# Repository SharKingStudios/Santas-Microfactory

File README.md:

# Santas Microfactory
A factory game built entirely out of diode transistor logic.

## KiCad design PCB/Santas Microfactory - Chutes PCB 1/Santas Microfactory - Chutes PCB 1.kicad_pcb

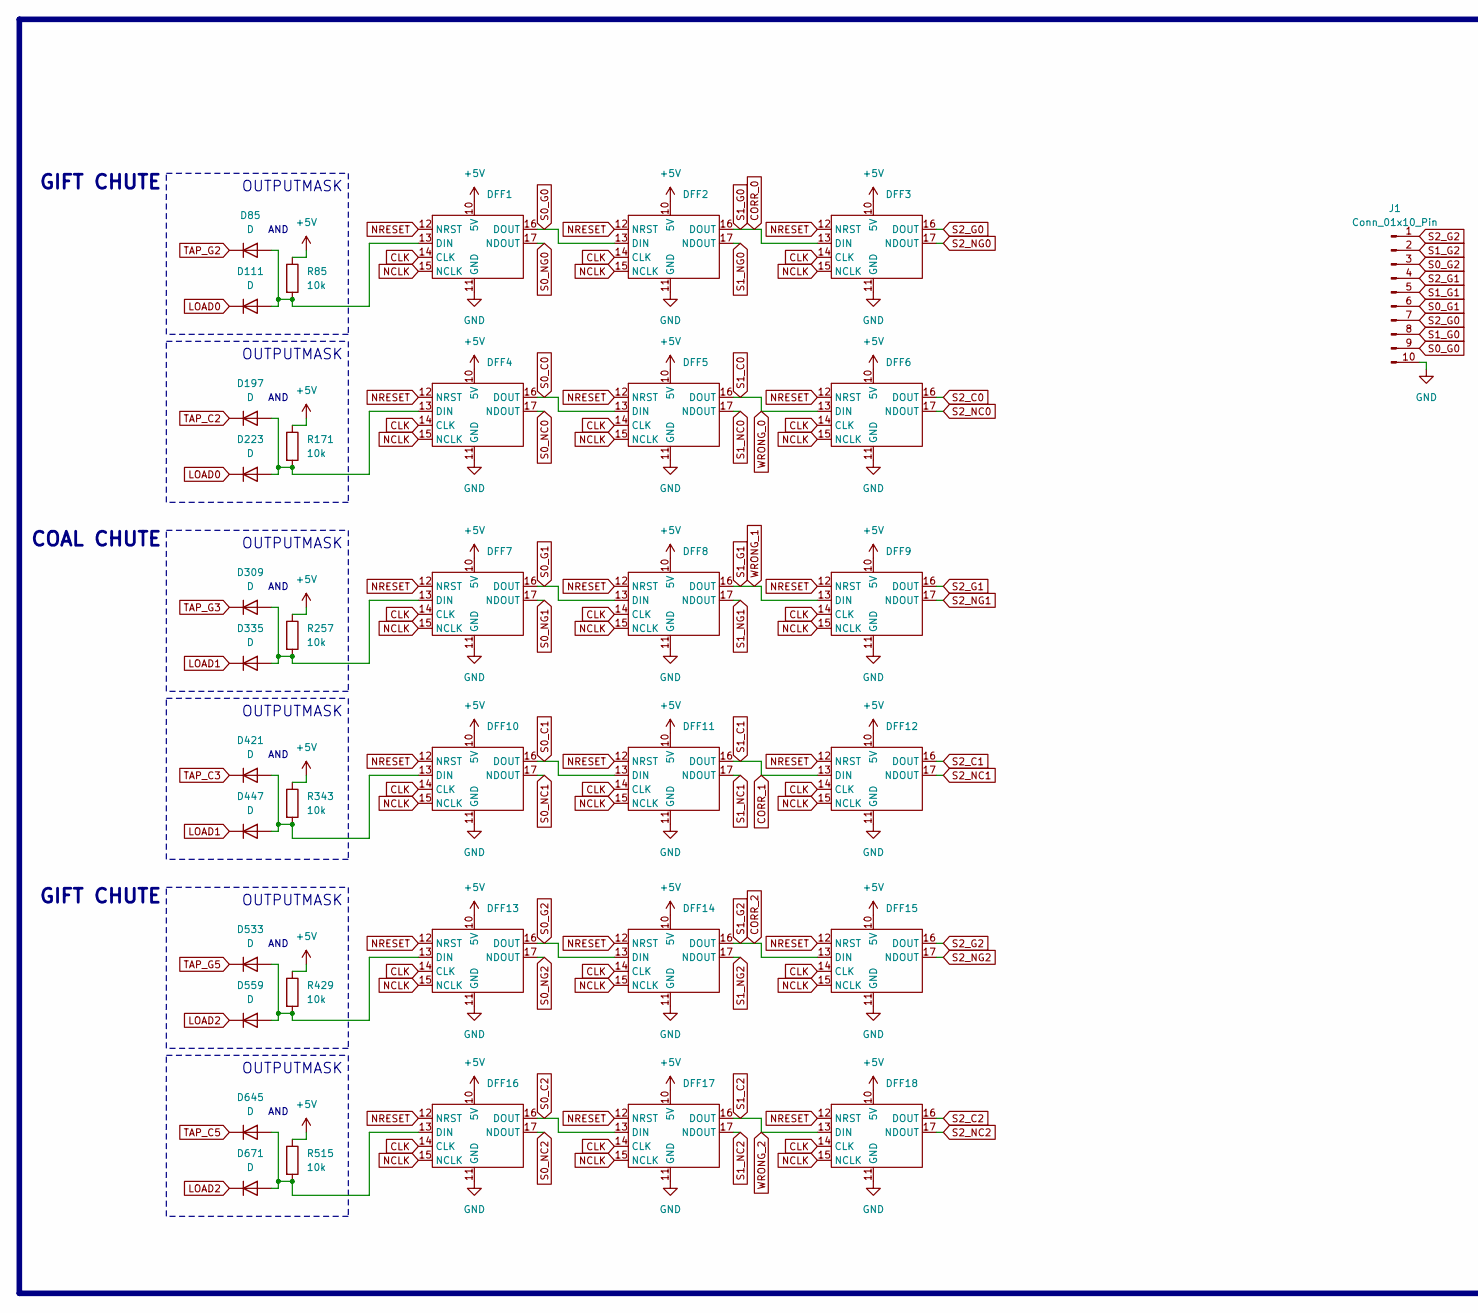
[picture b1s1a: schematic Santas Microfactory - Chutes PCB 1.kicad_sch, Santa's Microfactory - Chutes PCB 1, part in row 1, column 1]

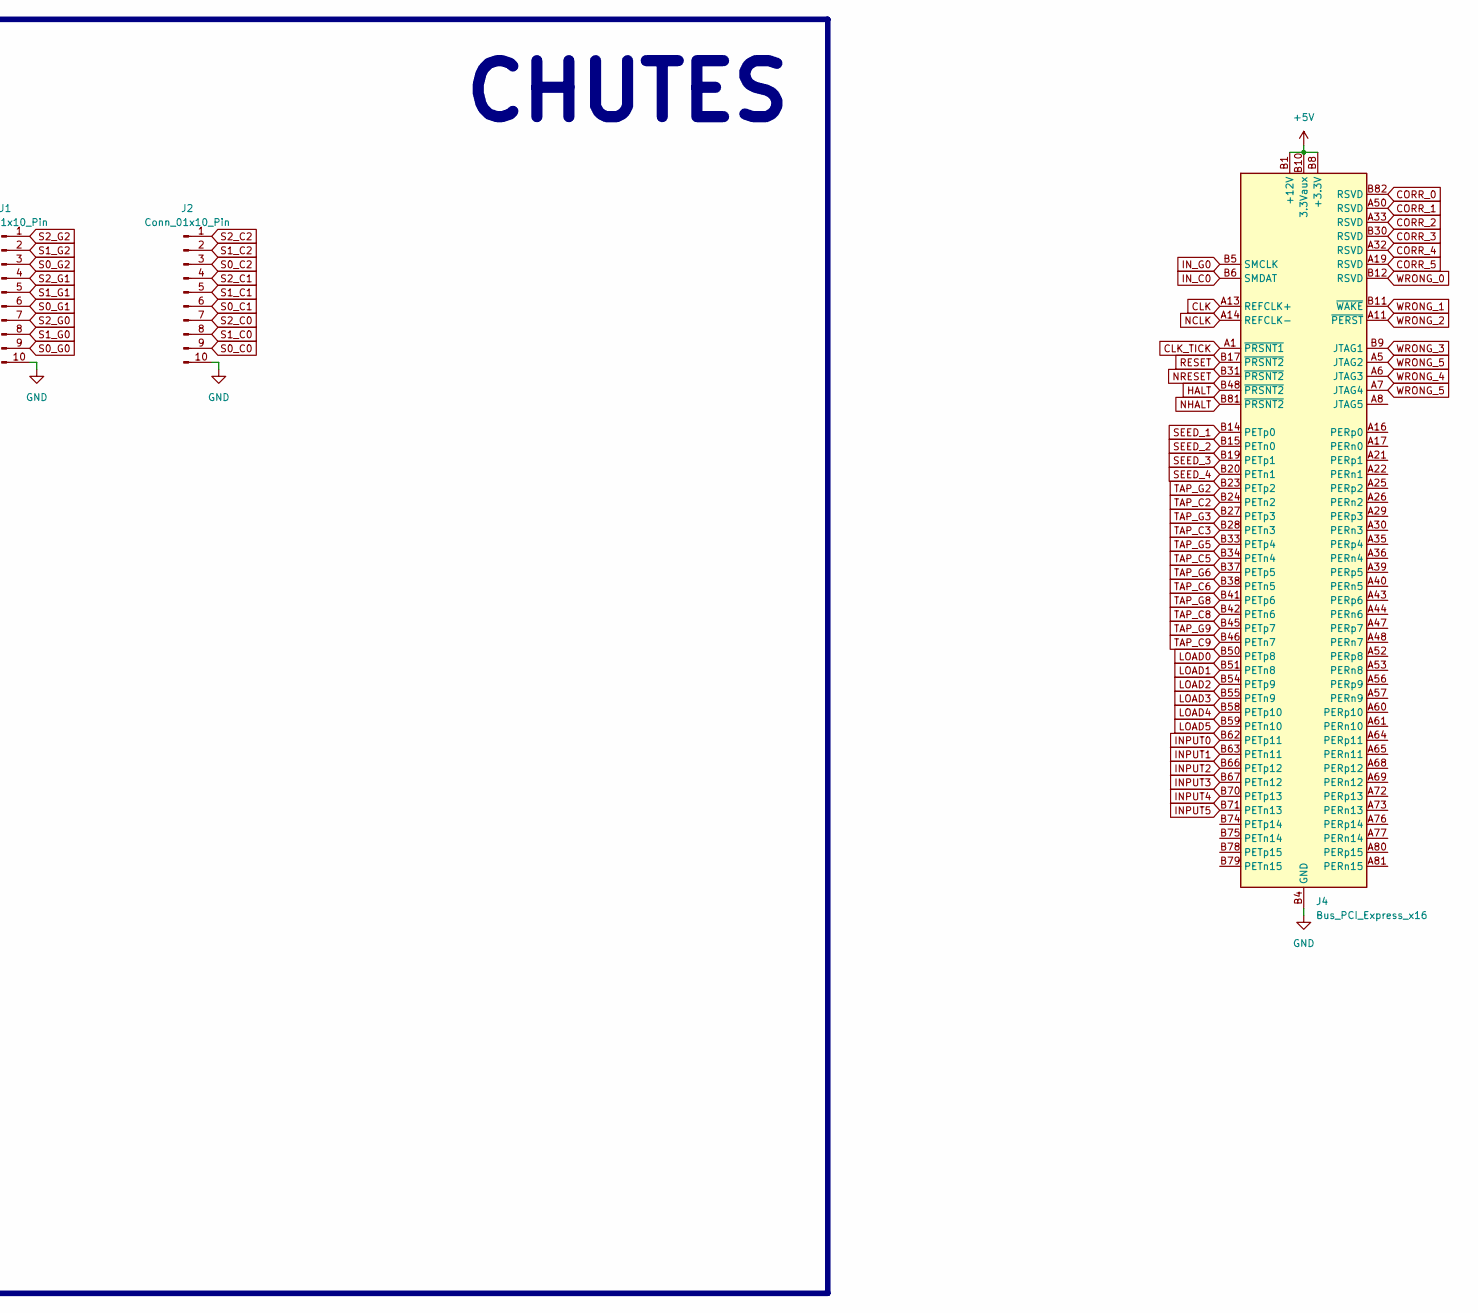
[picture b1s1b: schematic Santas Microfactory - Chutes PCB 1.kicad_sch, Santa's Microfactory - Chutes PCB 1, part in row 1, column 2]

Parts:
D85, D111, D197, D223, D309, D335, D421, D447, D533, D559, D645, D671: D; D_DO-35_SOD27_P2.54mm_Vertical_AnodeUp
DFF1, DFF2, DFF3, DFF4, DFF5, DFF6, DFF7, DFF8, DFF9, DFF10, DFF11, DFF12, DFF13, DFF14, DFF15, DFF16, DFF17, DFF18: DFF-shenanigans
J1, J2: Conn_01x10_Pin; PinHeader_1x10_P2.54mm_Horizontal
J4: Bus_PCI_Express_x16; BUS_PCIexpress_x16
R85, R171, R257, R343, R429, R515: 10k; R_Axial_DIN0207_L6.3mm_D2.5mm_P2.54mm_Vertical

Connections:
+5V: DFF1.10 (5V), DFF2.10 (5V), DFF3.10 (5V), DFF4.10 (5V), DFF5.10 (5V), DFF6.10 (5V), DFF7.10 (5V), DFF8.10 (5V), DFF9.10 (5V), DFF10.10 (5V), DFF11.10 (5V), DFF12.10 (5V), DFF13.10 (5V), DFF14.10 (5V), DFF15.10 (5V), DFF16.10 (5V), DFF17.10 (5V), DFF18.10 (5V), J4.A2 (+12V), J4.A3 (+12V), J4.A9 (+3.3V), J4.A10 (+3.3V), J4.B1 (+12V), J4.B2 (+12V), J4.B3 (+12V), J4.B8 (+3.3V), J4.B10 (3.3Vaux), R85.1, R171.1, R257.1, R343.1, R429.1, R515.1
CLK: DFF1.14 (CLK), DFF2.14 (CLK), DFF3.14 (CLK), DFF4.14 (CLK), DFF5.14 (CLK), DFF6.14 (CLK), DFF7.14 (CLK), DFF8.14 (CLK), DFF9.14 (CLK), DFF10.14 (CLK), DFF11.14 (CLK), DFF12.14 (CLK), DFF13.14 (CLK), DFF14.14 (CLK), DFF15.14 (CLK), DFF16.14 (CLK), DFF17.14 (CLK), DFF18.14 (CLK), J4.A13 (REFCLK+)
CLK_TICK: J4.A1 (~PRSNT1)
CORR_0: DFF2.16 (DOUT), DFF3.13 (DIN), J1.8, J4.B82 (RSVD)
CORR_1: DFF11.16 (DOUT), DFF12.13 (DIN), J2.5, J4.A50 (RSVD)
CORR_2: DFF14.16 (DOUT), DFF15.13 (DIN), J1.2, J4.A33 (RSVD)
CORR_3: J4.B30 (RSVD)
CORR_4: J4.A32 (RSVD)
CORR_5: J4.A19 (RSVD)
GND: DFF1.11 (GND), DFF2.11 (GND), DFF3.11 (GND), DFF4.11 (GND), DFF5.11 (GND), DFF6.11 (GND), DFF7.11 (GND), DFF8.11 (GND), DFF9.11 (GND), DFF10.11 (GND), DFF11.11 (GND), DFF12.11 (GND), DFF13.11 (GND), DFF14.11 (GND), DFF15.11 (GND), DFF16.11 (GND), DFF17.11 (GND), DFF18.11 (GND), J1.10, J2.10, J4.A4 (GND), J4.A12 (GND), J4.A15 (GND), J4.A18 (GND), J4.A20 (GND), J4.A23 (GND), J4.A24 (GND), J4.A27 (GND), J4.A28 (GND), J4.A31 (GND), J4.A34 (GND), J4.A37 (GND), J4.A38 (GND), J4.A41 (GND), J4.A42 (GND), J4.A45 (GND), J4.A46 (GND), J4.A49 (GND), J4.A51 (GND), J4.A54 (GND), J4.A55 (GND), J4.A58 (GND), J4.A59 (GND), J4.A62 (GND), J4.A63 (GND), J4.A66 (GND), J4.A67 (GND), J4.A70 (GND), J4.A71 (GND), J4.A74 (GND), J4.A75 (GND), J4.A78 (GND), J4.A79 (GND), J4.A82 (GND), J4.B4 (GND), J4.B7 (GND), J4.B13 (GND), J4.B16 (GND), J4.B18 (GND), J4.B21 (GND), J4.B22 (GND), J4.B25 (GND), J4.B26 (GND), J4.B29 (GND), J4.B32 (GND), J4.B35 (GND), J4.B36 (GND), J4.B39 (GND), J4.B40 (GND), J4.B43 (GND), J4.B44 (GND), J4.B47 (GND), J4.B49 (GND), J4.B52 (GND), J4.B53 (GND), J4.B56 (GND), J4.B57 (GND), J4.B60 (GND), J4.B61 (GND), J4.B64 (GND), J4.B65 (GND), J4.B68 (GND), J4.B69 (GND), J4.B72 (GND), J4.B73 (GND), J4.B76 (GND), J4.B77 (GND), J4.B80 (GND)
HALT: J4.B48 (~PRSNT2)
INPUT0: J4.B62 (PETp11)
INPUT1: J4.B63 (PETn11)
INPUT2: J4.B66 (PETp12)
INPUT3: J4.B67 (PETn12)
INPUT4: J4.B70 (PETp13)
INPUT5: J4.B71 (PETn13)
IN_C0: J4.B6 (SMDAT)
IN_G0: J4.B5 (SMCLK)
LOAD0: D111.1 (K), D223.1 (K), J4.B50 (PETp8)
LOAD1: D335.1 (K), D447.1 (K), J4.B51 (PETn8)
LOAD2: D559.1 (K), D671.1 (K), J4.B54 (PETp9)
LOAD3: J4.B55 (PETn9)
LOAD4: J4.B58 (PETp10)
LOAD5: J4.B59 (PETn10)
NCLK: DFF1.15 (NCLK), DFF2.15 (NCLK), DFF3.15 (NCLK), DFF4.15 (NCLK), DFF5.15 (NCLK), DFF6.15 (NCLK), DFF7.15 (NCLK), DFF8.15 (NCLK), DFF9.15 (NCLK), DFF10.15 (NCLK), DFF11.15 (NCLK), DFF12.15 (NCLK), DFF13.15 (NCLK), DFF14.15 (NCLK), DFF15.15 (NCLK), DFF16.15 (NCLK), DFF17.15 (NCLK), DFF18.15 (NCLK), J4.A14 (REFCLK-)
NHALT: J4.B81 (~PRSNT2)
NRESET: DFF1.12 (NRST), DFF2.12 (NRST), DFF3.12 (NRST), DFF4.12 (NRST), DFF5.12 (NRST), DFF6.12 (NRST), DFF7.12 (NRST), DFF8.12 (NRST), DFF9.12 (NRST), DFF10.12 (NRST), DFF11.12 (NRST), DFF12.12 (NRST), DFF13.12 (NRST), DFF14.12 (NRST), DFF15.12 (NRST), DFF16.12 (NRST), DFF17.12 (NRST), DFF18.12 (NRST), J4.B31 (~PRSNT2)
unnamed: D85.2 (A), D111.2 (A), DFF1.13 (DIN), R85.2
unnamed: D197.2 (A), D223.2 (A), DFF4.13 (DIN), R171.2
unnamed: D309.2 (A), D335.2 (A), DFF7.13 (DIN), R257.2
unnamed: D421.2 (A), D447.2 (A), DFF10.13 (DIN), R343.2
unnamed: D533.2 (A), D559.2 (A), DFF13.13 (DIN), R429.2
unnamed: D645.2 (A), D671.2 (A), DFF16.13 (DIN), R515.2
RESET: J4.B17 (~PRSNT2)
S0_C0: DFF4.16 (DOUT), DFF5.13 (DIN), J2.9
S0_C1: DFF10.16 (DOUT), DFF11.13 (DIN), J2.6
S0_C2: DFF16.16 (DOUT), DFF17.13 (DIN), J2.3
S0_G0: DFF1.16 (DOUT), DFF2.13 (DIN), J1.9
S0_G1: DFF7.16 (DOUT), DFF8.13 (DIN), J1.6
S0_G2: DFF13.16 (DOUT), DFF14.13 (DIN), J1.3
S0_NC0: DFF4.17 (NDOUT)
S0_NC1: DFF10.17 (NDOUT)
S0_NC2: DFF16.17 (NDOUT)
S0_NG0: DFF1.17 (NDOUT)
S0_NG1: DFF7.17 (NDOUT)
S0_NG2: DFF13.17 (NDOUT)
S1_C0: DFF5.16 (DOUT), DFF6.13 (DIN), J2.8, J4.B12 (RSVD)
S1_C2: DFF17.16 (DOUT), DFF18.13 (DIN), J2.2, J4.A11 (~PERST)
S1_G1: DFF8.16 (DOUT), DFF9.13 (DIN), J1.5, J4.B11 (~WAKE)
S1_NC0: DFF5.17 (NDOUT)
S1_NC1: DFF11.17 (NDOUT)
S1_NC2: DFF17.17 (NDOUT)
S1_NG0: DFF2.17 (NDOUT)
S1_NG1: DFF8.17 (NDOUT)
S1_NG2: DFF14.17 (NDOUT)
S2_C0: DFF6.16 (DOUT), J2.7
S2_C1: DFF12.16 (DOUT), J2.4
S2_C2: DFF18.16 (DOUT), J2.1
S2_G0: DFF3.16 (DOUT), J1.7
S2_G1: DFF9.16 (DOUT), J1.4
S2_G2: DFF15.16 (DOUT), J1.1
S2_NC0: DFF6.17 (NDOUT)
S2_NC1: DFF12.17 (NDOUT)
S2_NC2: DFF18.17 (NDOUT)
S2_NG0: DFF3.17 (NDOUT)
S2_NG1: DFF9.17 (NDOUT)
S2_NG2: DFF15.17 (NDOUT)
SEED_1: J4.B14 (PETp0)
SEED_2: J4.B15 (PETn0)
SEED_3: J4.B19 (PETp1)
SEED_4: J4.B20 (PETn1)
TAP_C2: D197.1 (K), J4.B24 (PETn2)
TAP_C3: D421.1 (K), J4.B28 (PETn3)
TAP_C5: D645.1 (K), J4.B34 (PETn4)
TAP_C6: J4.B38 (PETn5)
TAP_C8: J4.B42 (PETn6)
TAP_C9: J4.B46 (PETn7)
TAP_G2: D85.1 (K), J4.B23 (PETp2)
TAP_G3: D309.1 (K), J4.B27 (PETp3)
TAP_G5: D533.1 (K), J4.B33 (PETp4)
TAP_G6: J4.B37 (PETp5)
TAP_G8: J4.B41 (PETp6)
TAP_G9: J4.B45 (PETp7)
WRONG_3: J4.B9 (JTAG1)
WRONG_4: J4.A6 (JTAG3)
WRONG_5: J4.A5 (JTAG2), J4.A7 (JTAG4)

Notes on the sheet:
AND
OUTPUTMASK
GIFT CHUTE
COAL CHUTE
CHUTES

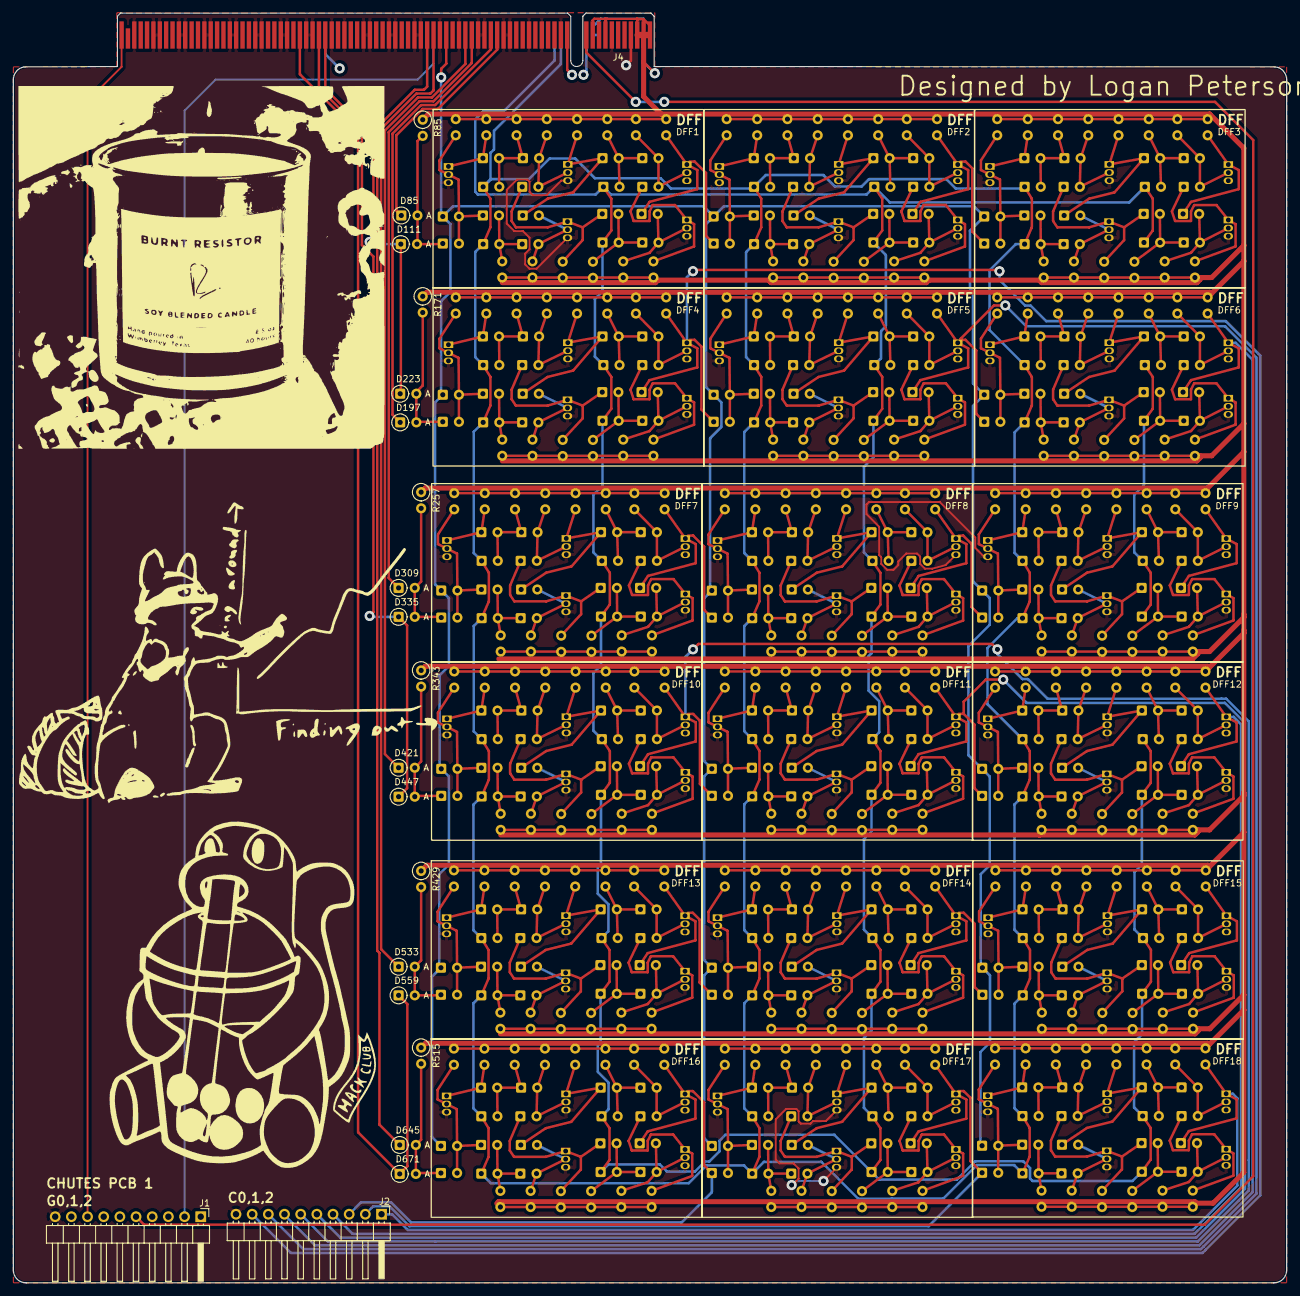
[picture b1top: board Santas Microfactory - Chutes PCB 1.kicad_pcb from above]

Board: 4 copper layers, 200.0 x 199.4 mm, 39 parts (0 on the bottom side), 39 nets.

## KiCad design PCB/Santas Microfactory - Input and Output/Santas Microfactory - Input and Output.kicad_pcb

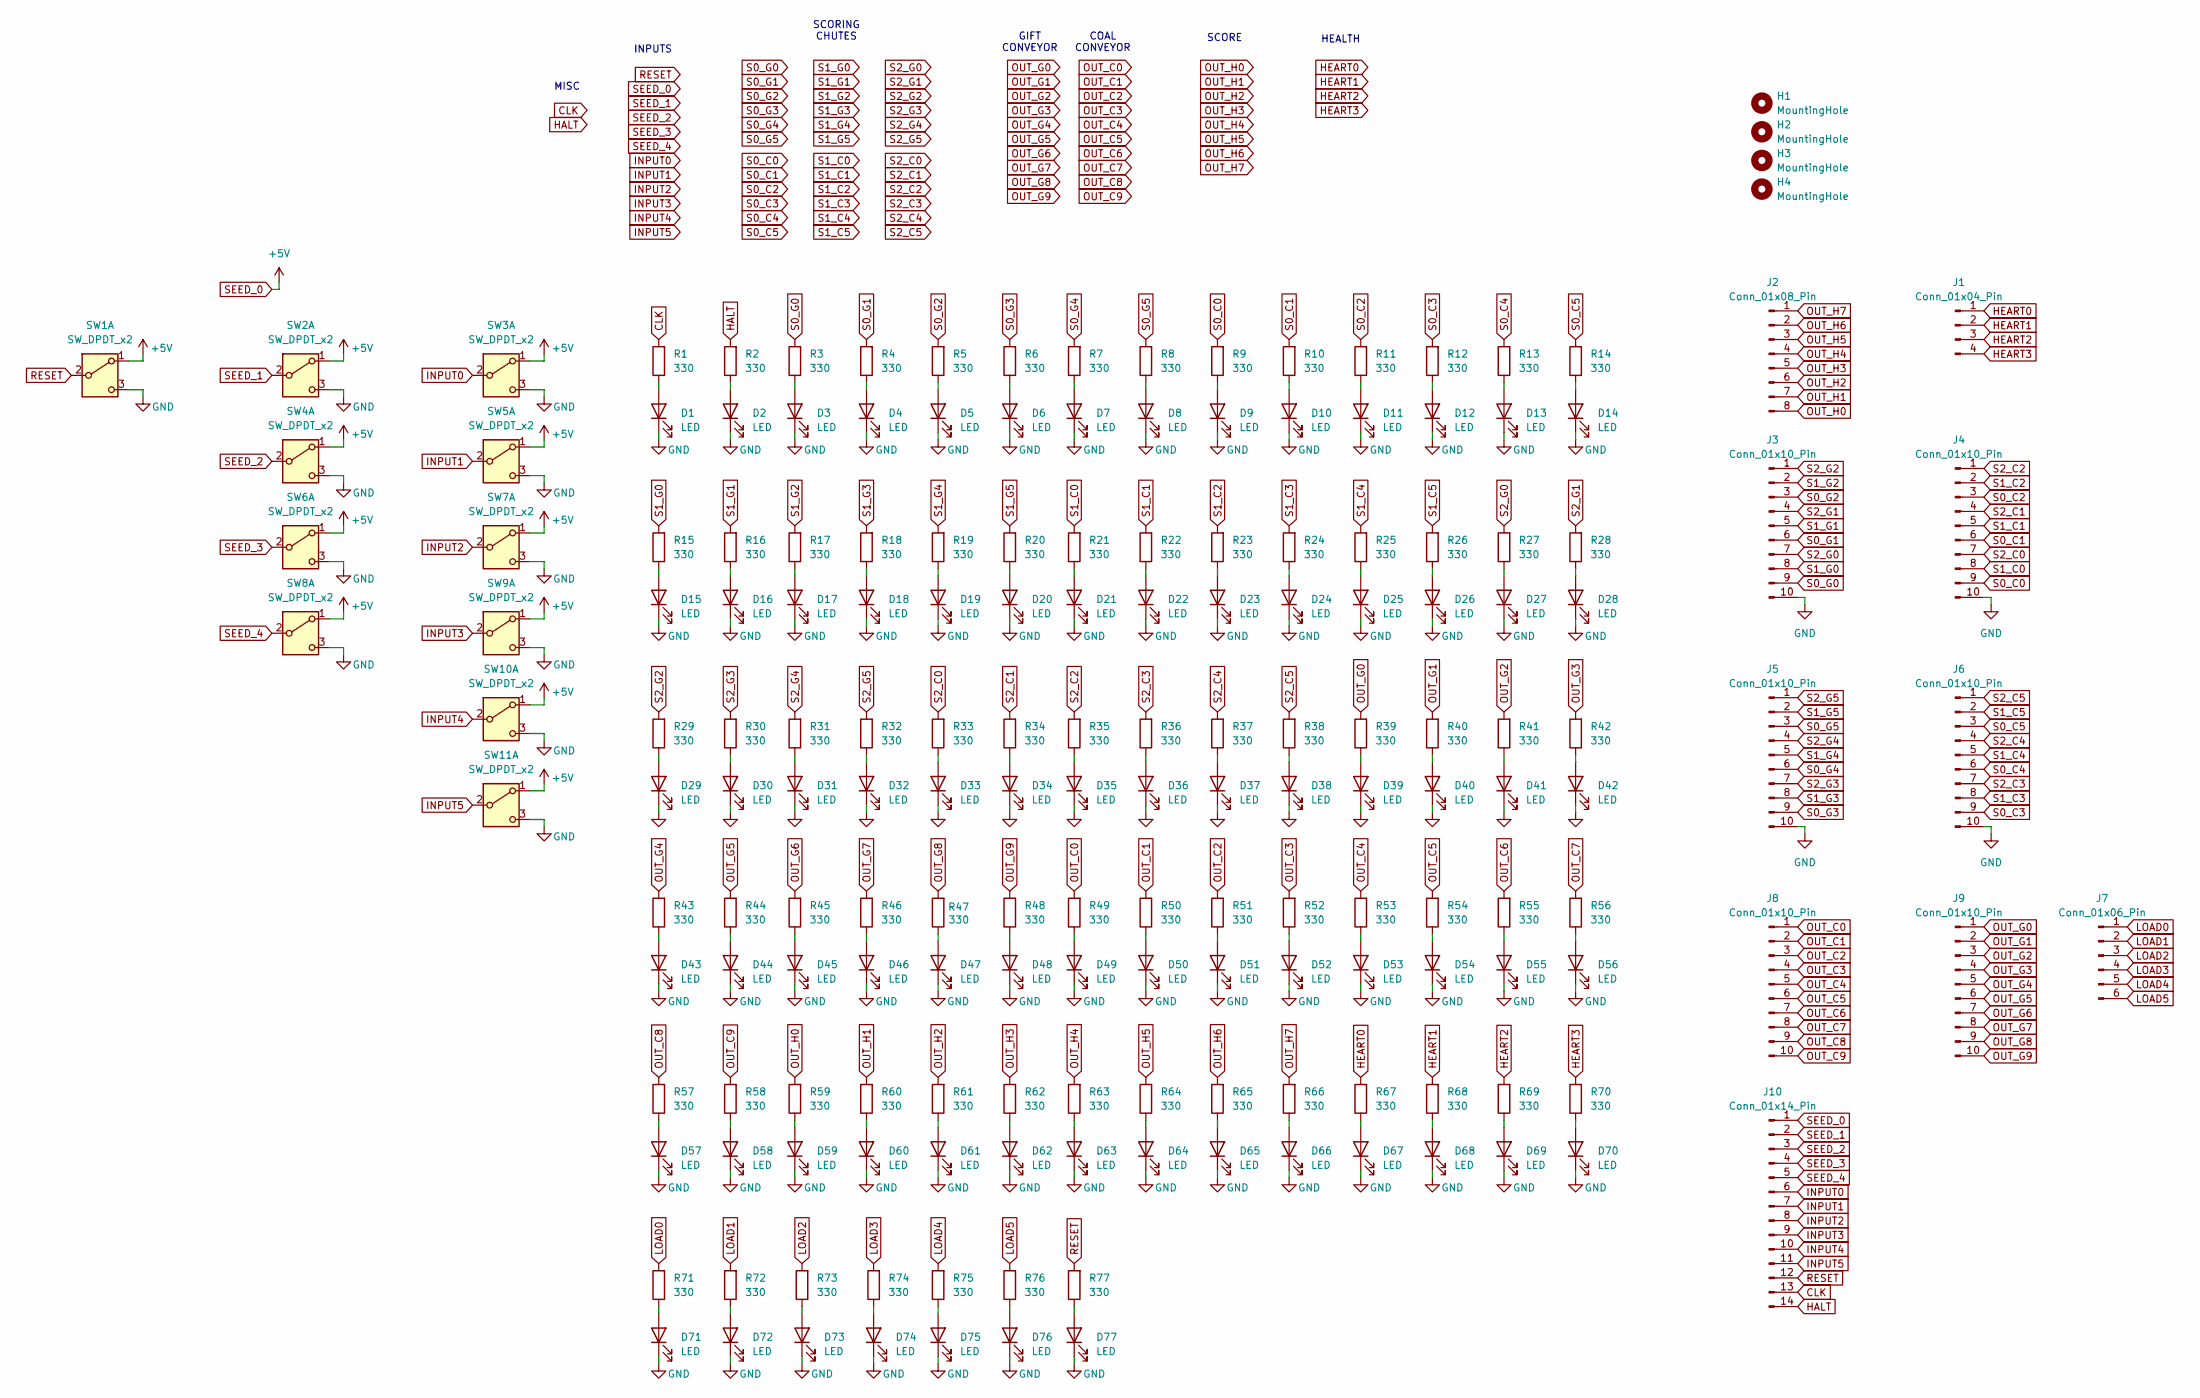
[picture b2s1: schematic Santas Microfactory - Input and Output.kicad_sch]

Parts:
D1, D2, D3, D4, D5, D6, D7, D8, D9, D10, D11, D12, D13, D14, D15, D16, D17, D18, D19, D20, D21, D22, D23, D24, D25, D26, D27, D28, D29, D30, D31, D32, D33, D34, D35, D36, D37, D38, D39, D40, D41, D42, D43, D44, D45, D46, D47, D48, D49, D50, D51, D52, D53, D54, D55, D56, D57, D58, D59, D60, D61, D62, D63, D64, D65, D66, D67, D68, D69, D70, D71, D72, D73, D74, D75, D76, D77: LED; LED_Rectangular_W5.0mm_H2.0mm
H1, H2, H3, H4: MountingHole; MountingHole_3.2mm_M3_Pad_Via
J1: Conn_01x04_Pin; PinHeader_1x04_P2.54mm_Vertical
J2: Conn_01x08_Pin; PinHeader_1x08_P2.54mm_Vertical
J3, J4, J5, J6, J8, J9: Conn_01x10_Pin; PinHeader_1x10_P2.54mm_Vertical
J7: Conn_01x06_Pin; PinHeader_1x06_P2.54mm_Vertical
J10: Conn_01x14_Pin; PinHeader_1x14_P2.54mm_Vertical
R1, R2, R3, R4, R5, R6, R7, R8, R9, R10, R11, R12, R13, R14, R15, R16, R17, R18, R19, R20, R21, R22, R23, R24, R25, R26, R27, R28, R29, R30, R31, R32, R33, R34, R35, R36, R37, R38, R39, R40, R41, R42, R43, R44, R45, R46, R47, R48, R49, R50, R51, R52, R53, R54, R55, R56, R57, R58, R59, R60, R61, R62, R63, R64, R65, R66, R67, R68, R69, R70, R71, R72, R73, R74, R75, R76, R77: 330; R_Axial_DIN0207_L6.3mm_D2.5mm_P10.16mm_Horizontal
SW1, SW2, SW3, SW4, SW5, SW6, SW7, SW8, SW9, SW10, SW11: SW_DPDT_x2; SW-TH_MT-0-103-A101-M200-RS

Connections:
CLK: J10.13, R1.2
GND: D1.1 (K), D2.1 (K), D3.1 (K), D4.1 (K), D5.1 (K), D6.1 (K), D7.1 (K), D8.1 (K), D9.1 (K), D10.1 (K), D11.1 (K), D12.1 (K), D13.1 (K), D14.1 (K), D15.1 (K), D16.1 (K), D17.1 (K), D18.1 (K), D19.1 (K), D20.1 (K), D21.1 (K), D22.1 (K), D23.1 (K), D24.1 (K), D25.1 (K), D26.1 (K), D27.1 (K), D28.1 (K), D29.1 (K), D30.1 (K), D31.1 (K), D32.1 (K), D33.1 (K), D34.1 (K), D35.1 (K), D36.1 (K), D37.1 (K), D38.1 (K), D39.1 (K), D40.1 (K), D41.1 (K), D42.1 (K), D43.1 (K), D44.1 (K), D45.1 (K), D46.1 (K), D47.1 (K), D48.1 (K), D49.1 (K), D50.1 (K), D51.1 (K), D52.1 (K), D53.1 (K), D54.1 (K), D55.1 (K), D56.1 (K), D57.1 (K), D58.1 (K), D59.1 (K), D60.1 (K), D61.1 (K), D62.1 (K), D63.1 (K), D64.1 (K), D65.1 (K), D66.1 (K), D67.1 (K), D68.1 (K), D69.1 (K), D70.1 (K), D71.1 (K), D72.1 (K), D73.1 (K), D74.1 (K), D75.1 (K), D76.1 (K), D77.1 (K), J3.10, J4.10, J5.10, J6.10, SW1.3 (C), SW2.3 (C), SW3.3 (C), SW4.3 (C), SW5.3 (C), SW6.3 (C), SW7.3 (C), SW8.3 (C), SW9.3 (C), SW10.3 (C), SW11.3 (C)
HALT: J10.14, R2.2
HEART0: J1.1, R67.2
HEART1: J1.2, R68.2
HEART2: J1.3, R69.2
HEART3: J1.4, R70.2
INPUT0: J10.6, SW3.2 (B)
INPUT1: J10.7, SW5.2 (B)
INPUT2: J10.8, SW7.2 (B)
INPUT3: J10.9, SW9.2 (B)
INPUT4: J10.10, SW10.2 (B)
INPUT5: J10.11, SW11.2 (B)
LOAD0: J7.1, R71.2
LOAD1: J7.2, R72.2
LOAD2: J7.3, R73.2
LOAD3: J7.4, R74.2
LOAD4: J7.5, R75.2
LOAD5: J7.6, R76.2
unnamed: D1.2 (A), R1.1
unnamed: D2.2 (A), R2.1
unnamed: D3.2 (A), R3.1
unnamed: D4.2 (A), R4.1
unnamed: D5.2 (A), R5.1
unnamed: D6.2 (A), R6.1
unnamed: D7.2 (A), R7.1
unnamed: D8.2 (A), R8.1
unnamed: D9.2 (A), R9.1
unnamed: D10.2 (A), R10.1
unnamed: D11.2 (A), R11.1
unnamed: D12.2 (A), R12.1
unnamed: D13.2 (A), R13.1
unnamed: D14.2 (A), R14.1
unnamed: D15.2 (A), R15.1
unnamed: D16.2 (A), R16.1
unnamed: D17.2 (A), R17.1
unnamed: D18.2 (A), R18.1
unnamed: D19.2 (A), R19.1
unnamed: D20.2 (A), R20.1
unnamed: D21.2 (A), R21.1
unnamed: D22.2 (A), R22.1
unnamed: D23.2 (A), R23.1
unnamed: D24.2 (A), R24.1
unnamed: D25.2 (A), R25.1
unnamed: D26.2 (A), R26.1
unnamed: D27.2 (A), R27.1
unnamed: D28.2 (A), R28.1
unnamed: D29.2 (A), R29.1
unnamed: D30.2 (A), R30.1
unnamed: D31.2 (A), R31.1
unnamed: D32.2 (A), R32.1
unnamed: D33.2 (A), R33.1
unnamed: D34.2 (A), R34.1
unnamed: D35.2 (A), R35.1
unnamed: D36.2 (A), R36.1
unnamed: D37.2 (A), R37.1
unnamed: D38.2 (A), R38.1
unnamed: D39.2 (A), R39.1
unnamed: D40.2 (A), R40.1
unnamed: D41.2 (A), R41.1
unnamed: D42.2 (A), R42.1
unnamed: D43.2 (A), R43.1
unnamed: D44.2 (A), R44.1
unnamed: D45.2 (A), R45.1
unnamed: D46.2 (A), R46.1
unnamed: D47.2 (A), R47.1
unnamed: D48.2 (A), R48.1
unnamed: D49.2 (A), R49.1
unnamed: D50.2 (A), R50.1
unnamed: D51.2 (A), R51.1
unnamed: D52.2 (A), R52.1
unnamed: D53.2 (A), R53.1
unnamed: D54.2 (A), R54.1
unnamed: D55.2 (A), R55.1
unnamed: D56.2 (A), R56.1
unnamed: D57.2 (A), R57.1
unnamed: D58.2 (A), R58.1
unnamed: D59.2 (A), R59.1
unnamed: D60.2 (A), R60.1
unnamed: D61.2 (A), R61.1
unnamed: D62.2 (A), R62.1
unnamed: D63.2 (A), R63.1
unnamed: D64.2 (A), R64.1
unnamed: D65.2 (A), R65.1
unnamed: D66.2 (A), R66.1
unnamed: D67.2 (A), R67.1
unnamed: D68.2 (A), R68.1
unnamed: D69.2 (A), R69.1
unnamed: D70.2 (A), R70.1
unnamed: D71.2 (A), R71.1
unnamed: D72.2 (A), R72.1
unnamed: D73.2 (A), R73.1
unnamed: D74.2 (A), R74.1
unnamed: D75.2 (A), R75.1
unnamed: D76.2 (A), R76.1
unnamed: D77.2 (A), R77.1
OUT_C0: J8.1, R49.2
OUT_C1: J8.2, R50.2
OUT_C2: J8.3, R51.2
OUT_C3: J8.4, R52.2
OUT_C4: J8.5, R53.2
OUT_C5: J8.6, R54.2
OUT_C6: J8.7, R55.2
OUT_C7: J8.8, R56.2
OUT_C8: J8.9, R57.2
OUT_C9: J8.10, R58.2
OUT_G0: J9.1, R39.2
OUT_G1: J9.2, R40.2
OUT_G2: J9.3, R41.2
OUT_G3: J9.4, R42.2
OUT_G4: J9.5, R43.2
OUT_G5: J9.6, R44.2
OUT_G6: J9.7, R45.2
OUT_G7: J9.8, R46.2
OUT_G8: J9.9, R47.2
OUT_G9: J9.10, R48.2
OUT_H0: J2.8, R59.2
OUT_H1: J2.7, R60.2
OUT_H2: J2.6, R61.2
OUT_H3: J2.5, R62.2
OUT_H4: J2.4, R63.2
OUT_H5: J2.3, R64.2
OUT_H6: J2.2, R65.2
OUT_H7: J2.1, R66.2
RESET: J10.12, R77.2, SW1.2 (B)
S0_C0: J4.9, R9.2
S0_C1: J4.6, R10.2
S0_C2: J4.3, R11.2
S0_C3: J6.9, R12.2
S0_C4: J6.6, R13.2
S0_C5: J6.3, R14.2
S0_G0: J3.9, R3.2
S0_G1: J3.6, R4.2
S0_G2: J3.3, R5.2
S0_G3: J5.9, R6.2
S0_G4: J5.6, R7.2
S0_G5: J5.3, R8.2
S1_C0: J4.8, R21.2
S1_C1: J4.5, R22.2
S1_C2: J4.2, R23.2
S1_C3: J6.8, R24.2
S1_C4: J6.5, R25.2
S1_C5: J6.2, R26.2
S1_G0: J3.8, R15.2
S1_G1: J3.5, R16.2
S1_G2: J3.2, R17.2
S1_G3: J5.8, R18.2
S1_G4: J5.5, R19.2
S1_G5: J5.2, R20.2
S2_C0: J4.7, R33.2
S2_C1: J4.4, R34.2
S2_C2: J4.1, R35.2
S2_C3: J6.7, R36.2
S2_C4: J6.4, R37.2
S2_C5: J6.1, R38.2
S2_G0: J3.7, R27.2
S2_G1: J3.4, R28.2
S2_G2: J3.1, R29.2
S2_G3: J5.7, R30.2
S2_G4: J5.4, R31.2
S2_G5: J5.1, R32.2
SEED_0: J10.1, SW1.1 (A), SW2.1 (A), SW3.1 (A), SW4.1 (A), SW5.1 (A), SW6.1 (A), SW7.1 (A), SW8.1 (A), SW9.1 (A), SW10.1 (A), SW11.1 (A)
SEED_1: J10.2, SW2.2 (B)
SEED_2: J10.3, SW4.2 (B)
SEED_3: J10.4, SW6.2 (B)
SEED_4: J10.5, SW8.2 (B)

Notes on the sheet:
HEALTH
COAL CONVEYOR
SCORING CHUTES
INPUTS
SCORE
MISC
GIFT CONVEYOR

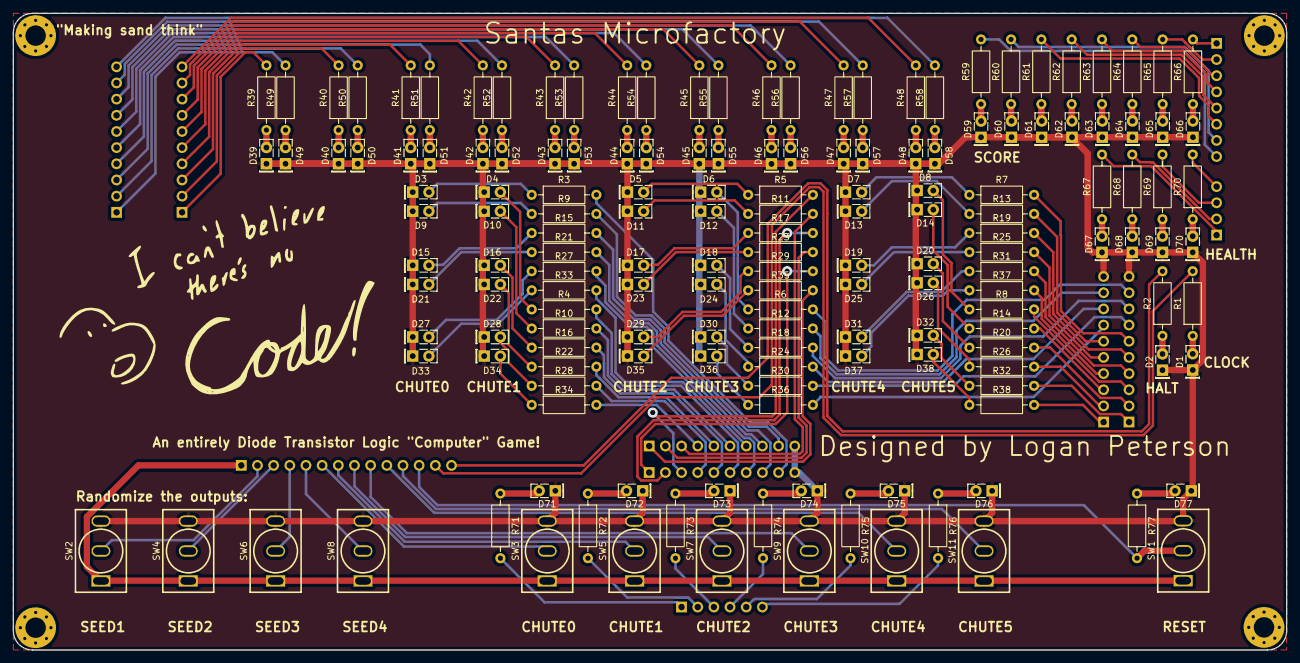
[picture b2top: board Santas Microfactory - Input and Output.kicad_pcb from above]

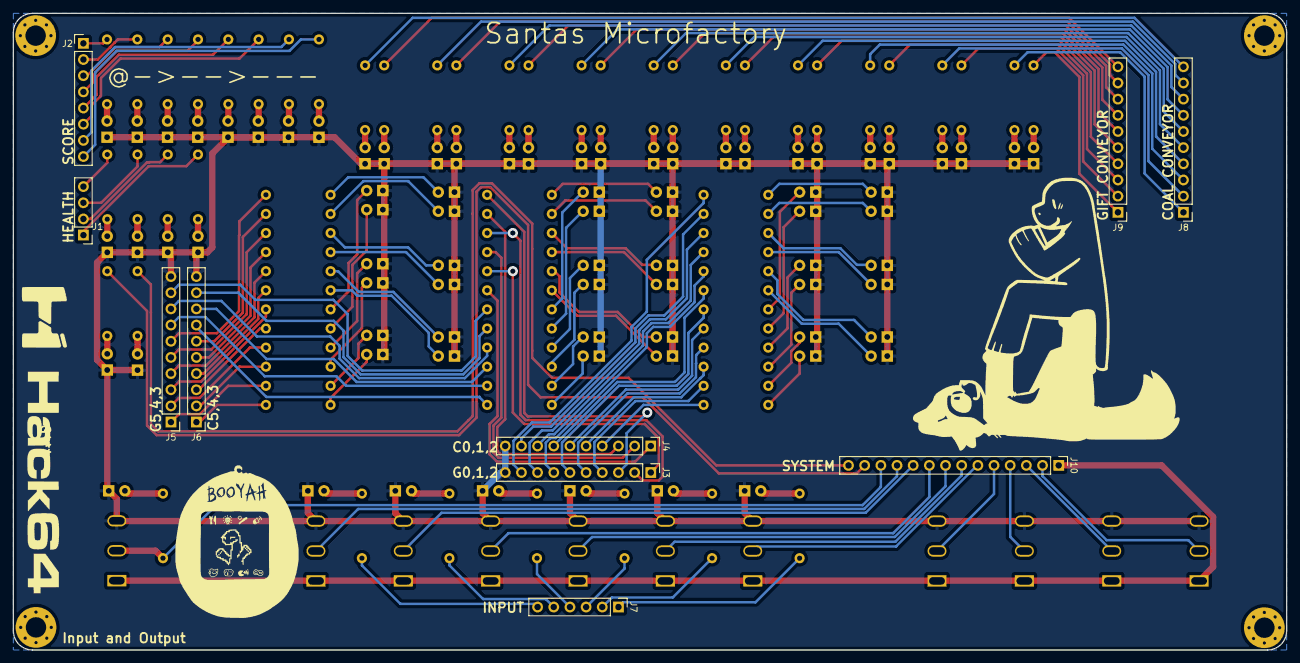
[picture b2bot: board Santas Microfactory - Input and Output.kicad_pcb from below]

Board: 2 copper layers, 200.0 x 100.0 mm, 179 parts (10 on the bottom side), 166 nets.
